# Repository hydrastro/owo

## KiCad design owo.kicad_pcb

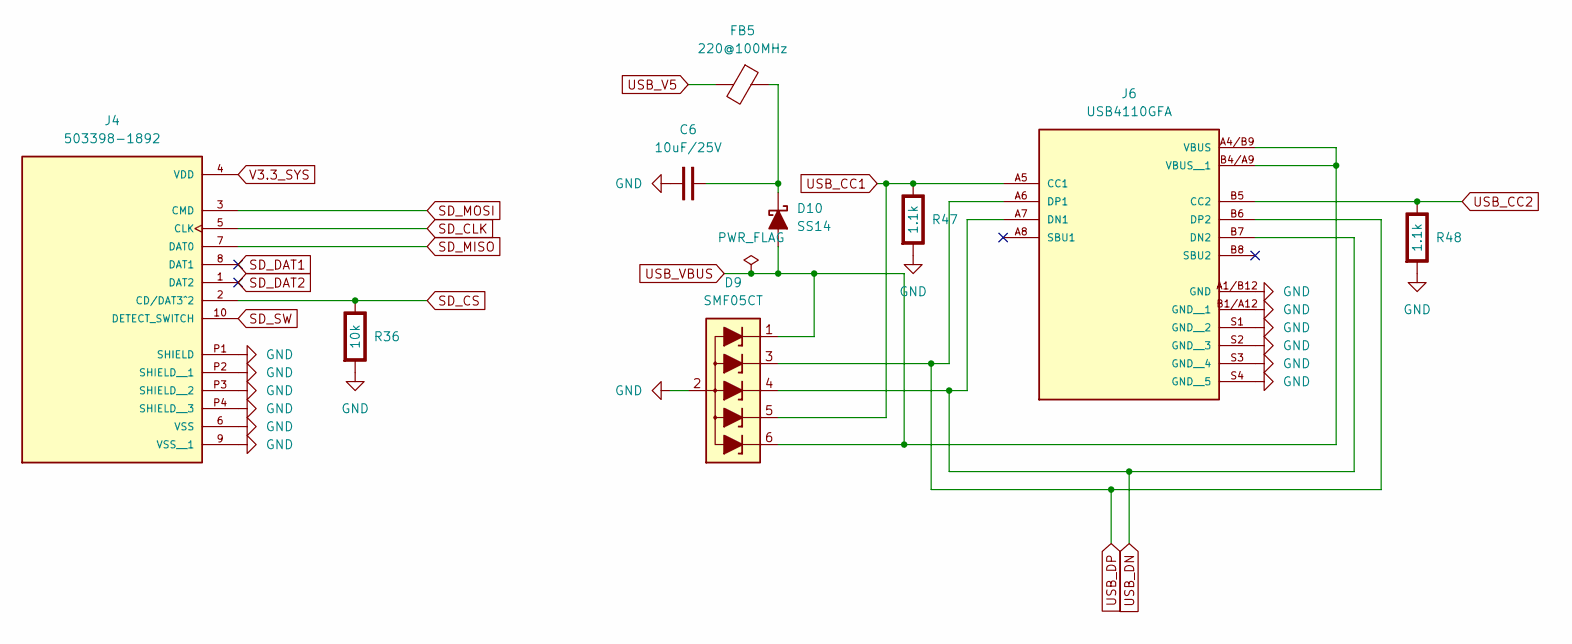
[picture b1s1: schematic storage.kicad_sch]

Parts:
C6: 10uF/25V; C_0805_2012Metric
D9: SMF05CT; SOT-363_SC-70-6
D10: SS14; D_SMA
FB5: 220@100MHz; Ferrite_0603_1608Metric
J4: 503398-1892; MOLEX_503398-1892; PARTREV 0
J6: USB4110GFA; GCT_USB4110GFA
R36: 10k; R_0603_1608Metric; Rating W
R47, R48: 1.1k; R_0603_1608Metric; Rating W

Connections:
unnamed: C6.2, D10.1 (K), FB5.1
SD_CLK: J4.5 (CLK); also elsewhere on the board
SD_CS: J4.2 (CD/DAT3^2), R36.1 (+); also elsewhere on the board
SD_DAT1: J4.8 (DAT1)
SD_DAT2: J4.1 (DAT2)
SD_MISO: J4.7 (DAT0); also elsewhere on the board
SD_MOSI: J4.3 (CMD); also elsewhere on the board
SD_SW: J4.10 (DETECT_SWITCH); also elsewhere on the board
USB_CC1: D9.5 (L4), J6.A5 (CC1), R47.1 (+)
USB_CC2: J6.B5 (CC2), R48.1 (+)
USB_DN: D9.4 (L3), J6.A7 (DN1), J6.B7 (DN2); also elsewhere on the board
USB_DP: D9.3 (L2), J6.A6 (DP1), J6.B6 (DP2); also elsewhere on the board
USB_V5: FB5.2; also elsewhere on the board
USB_VBUS: D9.1 (L1), D9.6 (L5), D10.2 (A), J6.A4/B9 (VBUS), J6.B4/A9 (VBUS__1)
V3.3_SYS: J4.4 (VDD); also elsewhere on the board

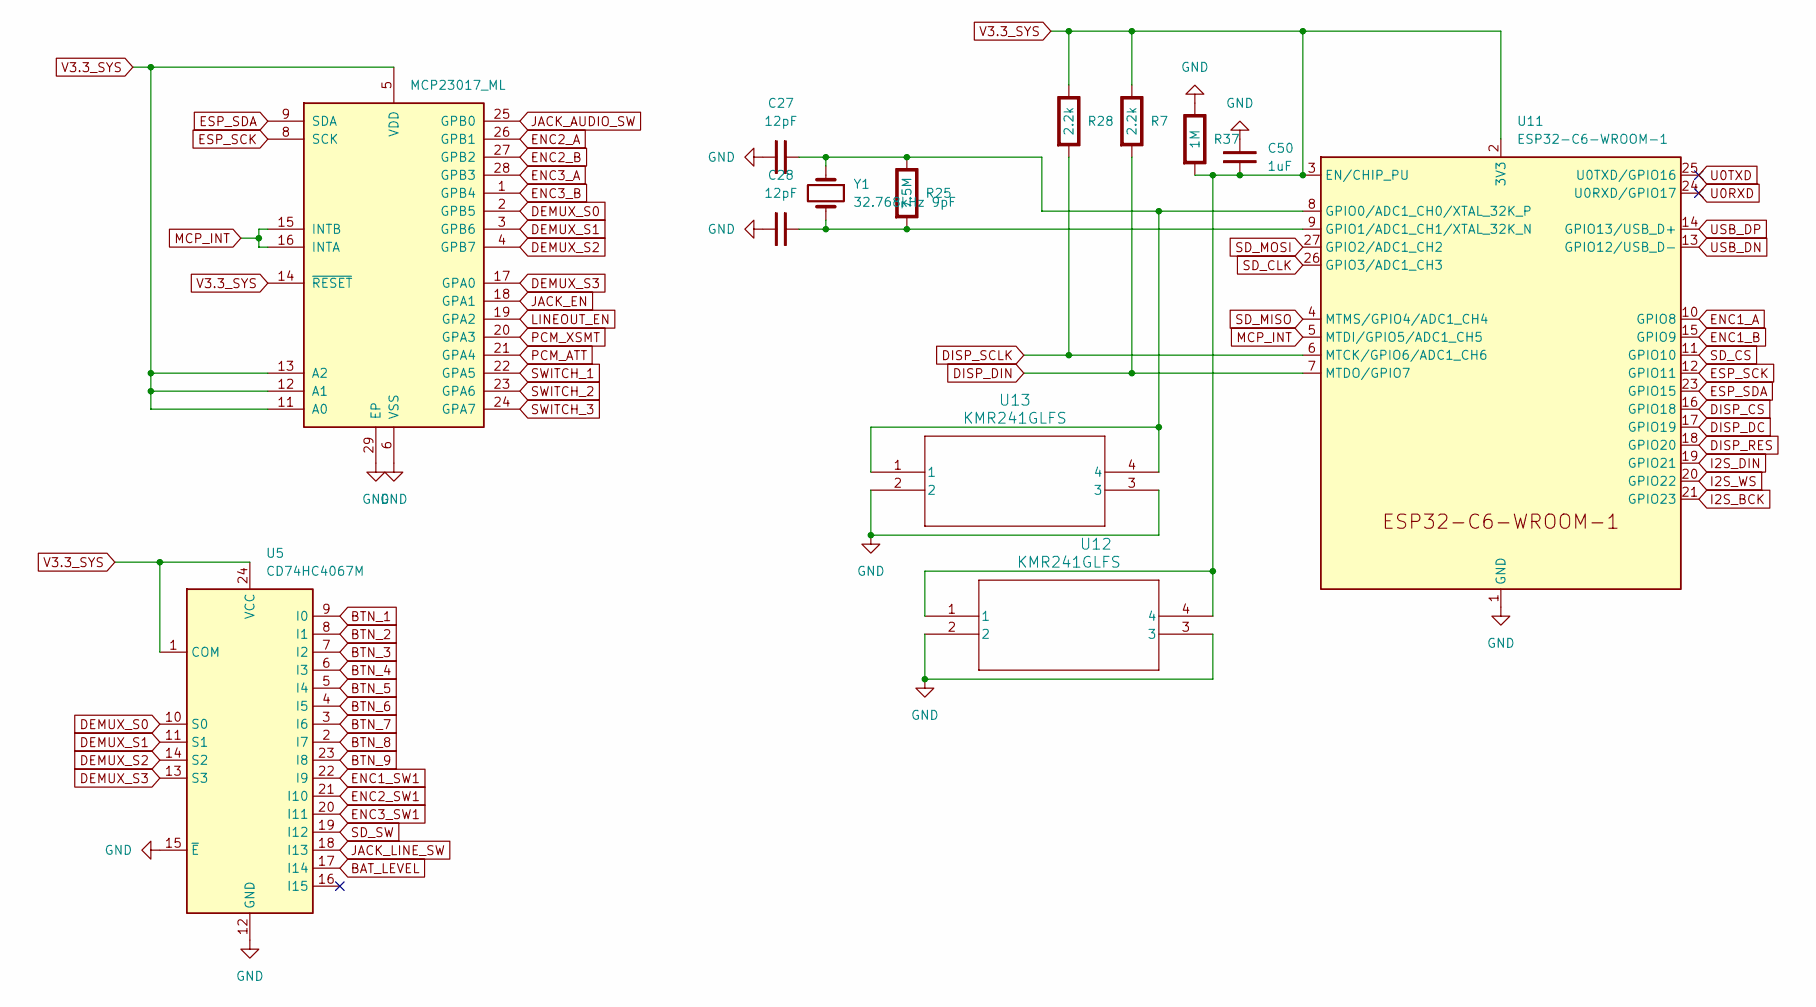
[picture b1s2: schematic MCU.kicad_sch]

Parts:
C27, C28: 12pF; C_0402_1005Metric
C50: 1uF; C_0603_1608Metric
R7, R28: 2.2k; R_0603_1608Metric; Rating W
R25: 7.5M; R_0603_1608Metric; Rating W
R37: 1M; R_0603_1608Metric; Rating W
U5: CD74HC4067M; SOIC-24W_7.5x15.4mm_P1.27mm
U10: MCP23017_ML; QFN-28-1EP_6x6mm_P0.65mm_EP4.25x4.25mm
U11: ESP32-C6-WROOM-1
U12, U13: KMR241GLFS; SWITCH_241GLFS
Y1: 32.768kHz 9pF; Crystal_SMD_0603-2Pin_6.0x3.5mm

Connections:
BAT_LEVEL: U5.17 (I14); also elsewhere on the board
BTN_1: U5.9 (I0); also elsewhere on the board
BTN_2: U5.8 (I1); also elsewhere on the board
BTN_3: U5.7 (I2); also elsewhere on the board
BTN_4: U5.6 (I3); also elsewhere on the board
BTN_5: U5.5 (I4); also elsewhere on the board
BTN_6: U5.4 (I5); also elsewhere on the board
BTN_7: U5.3 (I6); also elsewhere on the board
BTN_8: U5.2 (I7); also elsewhere on the board
BTN_9: U5.23 (I8); also elsewhere on the board
DEMUX_S0: U5.10 (S0), U10.2 (GPB5)
DEMUX_S1: U5.11 (S1), U10.3 (GPB6)
DEMUX_S2: U5.14 (S2), U10.4 (GPB7)
DEMUX_S3: U5.13 (S3), U10.17 (GPA0)
DISP_CS: U11.16 (GPIO18); also elsewhere on the board
DISP_DC: U11.17 (GPIO19); also elsewhere on the board
DISP_DIN: R7.2 (-), U11.7 (MTDO/GPIO7); also elsewhere on the board
DISP_RES: U11.18 (GPIO20); also elsewhere on the board
DISP_SCLK: R28.2 (-), U11.6 (MTCK/GPIO6/ADC1_CH6); also elsewhere on the board
ENC1_A: U11.10 (GPIO8); also elsewhere on the board
ENC1_B: U11.15 (GPIO9); also elsewhere on the board
ENC1_SW1: U5.22 (I9); also elsewhere on the board
ENC2_A: U10.26 (GPB1); also elsewhere on the board
ENC2_B: U10.27 (GPB2); also elsewhere on the board
ENC2_SW1: U5.21 (I10); also elsewhere on the board
ENC3_A: U10.28 (GPB3); also elsewhere on the board
ENC3_B: U10.1 (GPB4); also elsewhere on the board
ENC3_SW1: U5.20 (I11); also elsewhere on the board
ESP_SCK: U10.8 (SCK), U11.12 (GPIO11); also elsewhere on the board
ESP_SDA: U10.9 (SDA), U11.23 (GPIO15); also elsewhere on the board
I2S_BCK: U11.21 (GPIO23); also elsewhere on the board
I2S_DIN: U11.19 (GPIO21); also elsewhere on the board
I2S_WS: U11.20 (GPIO22); also elsewhere on the board
JACK_AUDIO_SW: U10.25 (GPB0); also elsewhere on the board
JACK_EN: U10.18 (GPA1); also elsewhere on the board
JACK_LINE_SW: U5.18 (I13); also elsewhere on the board
LINEOUT_EN: U10.19 (GPA2); also elsewhere on the board
MCP_INT: U10.15 (INTB), U10.16 (INTA), U11.5 (MTDI/GPIO5/ADC1_CH5)
unnamed: C27.2, R25.1 (+), U11.8 (GPIO0/ADC1_CH0/XTAL_32K_P), U13.1, U13.4, Y1.1
unnamed: C28.2, R25.2 (-), U11.9 (GPIO1/ADC1_CH1/XTAL_32K_N), Y1.2
PCM_ATT: U10.21 (GPA4); also elsewhere on the board
PCM_XSMT: U10.20 (GPA3); also elsewhere on the board
SD_CLK: U11.26 (GPIO3/ADC1_CH3); also elsewhere on the board
SD_CS: U11.11 (GPIO10); also elsewhere on the board
SD_MISO: U11.4 (MTMS/GPIO4/ADC1_CH4); also elsewhere on the board
SD_MOSI: U11.27 (GPIO2/ADC1_CH2); also elsewhere on the board
SD_SW: U5.19 (I12); also elsewhere on the board
SWITCH_1: U10.22 (GPA5); also elsewhere on the board
SWITCH_2: U10.23 (GPA6); also elsewhere on the board
SWITCH_3: U10.24 (GPA7); also elsewhere on the board
U0RXD: U11.24 (U0RXD/GPIO17)
U0TXD: U11.25 (U0TXD/GPIO16)
USB_DN: U11.13 (GPIO12/USB_D-); also elsewhere on the board
USB_DP: U11.14 (GPIO13/USB_D+); also elsewhere on the board
V3.3_SYS: C50.1, R7.1 (+), R28.1 (+), R37.2 (-), U5.1 (COM), U5.24 (VCC), U10.5 (VDD), U10.11 (A0), U10.12 (A1), U10.13 (A2), U10.14 (~RESET), U11.2 (3V3), U11.3 (EN/CHIP_PU), U12.1, U12.4; also elsewhere on the board

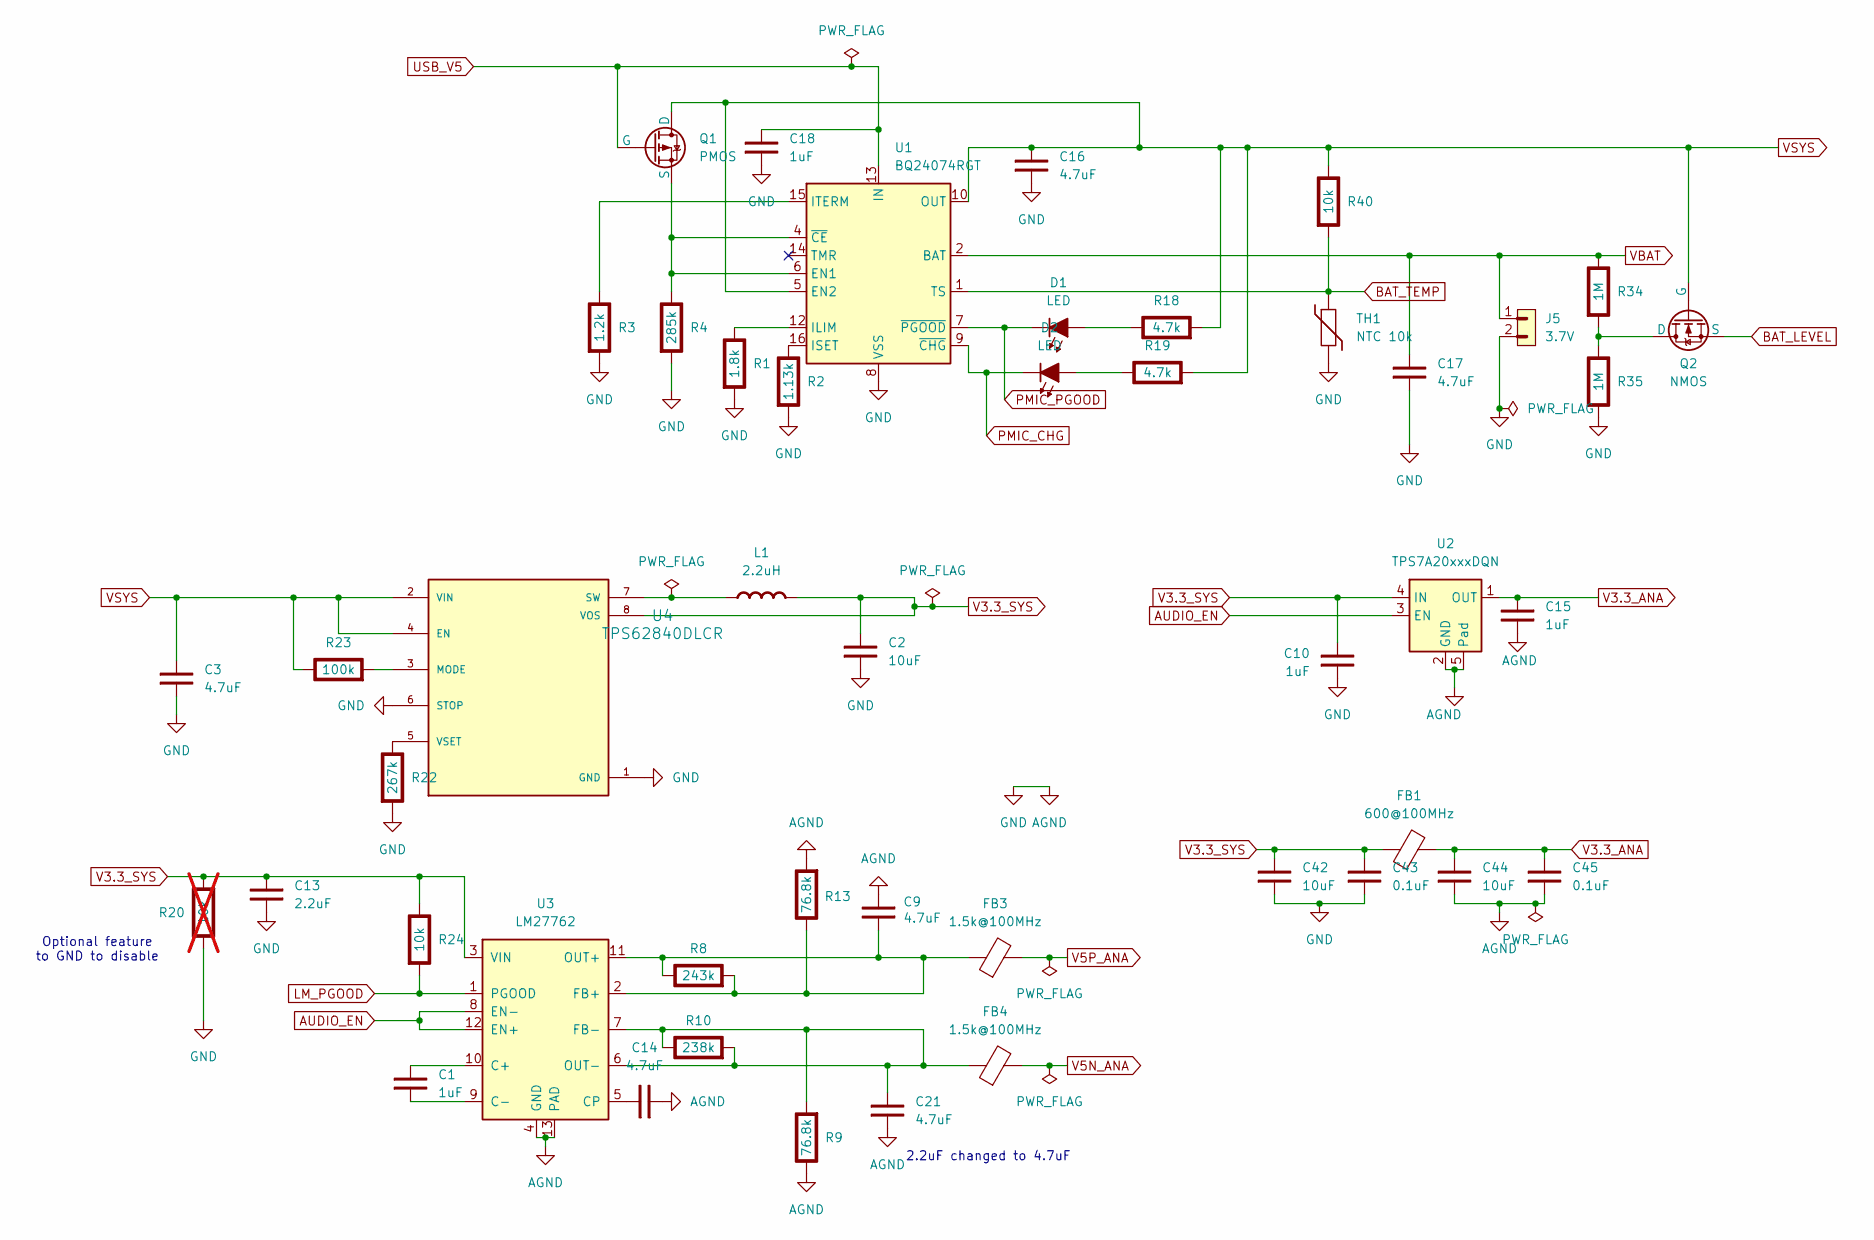
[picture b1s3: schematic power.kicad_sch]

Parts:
C1, C10, C15, C18: 1uF; C_0603_1608Metric
C2: 10uF; C_0805_2012Metric
C3, C9, C14, C16, C17, C21: 4.7uF; C_0603_1608Metric
C13: 2.2uF; C_0603_1608Metric
C42, C44: 10uF; CP_EIA-3528-21_Kemet-B
C43, C45: 0.1uF; C_0603_1608Metric
D1, D2: LED; LED_PLCC-2_2216
FB1: 600@100MHz; Ferrite_0805_2012Metric
FB3, FB4: 1.5k@100MHz; Ferrite_0603_1608Metric
J5: 3.7V; CONN_B2B-ZR-SM4-TF_JST
L1: 2.2uH; L_1008_2520Metric; Rating A
Q1: PMOS; SOT-23
Q2: NMOS; SOT-23
R1: 1.8k; R_0603_1608Metric; Rating W
R2: 1.13k; R_0603_1608Metric; Rating W
R3: 1.2k; R_0603_1608Metric; Rating W
R4: 285k; R_0603_1608Metric; Rating W
R8: 243k; R_0603_1608Metric; Rating W
R9, R13: 76.8k; R_0603_1608Metric; Rating W
R10: 238k; R_0603_1608Metric; Rating W
R18, R19: 4.7k; R_0603_1608Metric; Rating W
R20: 10k; R_0603_1608Metric; Rating W; not fitted
R22: 267k; R_0603_1608Metric; Rating W
R23: 100k; R_0603_1608Metric; Rating W
R24, R40: 10k; R_0603_1608Metric; Rating W
R34, R35: 1M; R_0603_1608Metric; Rating W
TH1: NTC 10k; R_0603_1608Metric
U1: BQ24074RGT; VQFN-16-1EP_3x3mm_P0.5mm_EP1.6x1.6mm
U2: TPS7A20xxxDQN; Texas_X2SON-4_1x1mm_P0.65mm
U3: LM27762; WSON-12-1EP_3x2mm_P0.5mm_EP1x2.65_ThermalVias
U4: TPS62840DLCR; SON50P200X150X100-8N

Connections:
AUDIO_EN: U2.3 (EN), U3.8 (EN-), U3.12 (EN+)
BAT_LEVEL: Q2.3 (S); also elsewhere on the board
BAT_TEMP: R40.2 (-), TH1.1, U1.1 (TS)
LM_PGOOD: R24.2 (-), U3.1 (PGOOD)
unnamed: D1.2 (A), R18.1 (+)
unnamed: D2.2 (A), R19.1 (+)
unnamed: L1.1 (+), U4.7 (SW)
unnamed: Q1.3 (S), R4.1 (+), U1.4 (~CE), U1.6 (EN1)
unnamed: Q2.1 (D), R34.2 (-), R35.1 (+)
unnamed: R1.1 (+), U1.12 (ILIM)
unnamed: R2.1 (+), U1.16 (ISET)
unnamed: R3.1 (+), U1.15 (ITERM)
unnamed: C21.2, FB4.1, R9.2 (-), R10.1 (+), R10.2 (-), U3.6 (OUT-), U3.7 (FB-)
unnamed: C9.2, FB3.1, R8.1 (+), R8.2 (-), R13.1 (+), U3.2 (FB+), U3.11 (OUT+)
unnamed: R22.1 (+), U4.5 (VSET)
unnamed: R23.2 (-), U4.3 (MODE)
unnamed: C1.2, U3.10 (C+)
unnamed: C1.1, U3.9 (C-)
unnamed: C14.2, U3.5 (CP)
PMIC_CHG: D2.1 (K), U1.9 (~CHG)
PMIC_PGOOD: D1.1 (K), U1.7 (~PGOOD)
USB_V5: C18.2, Q1.2 (G), U1.13 (IN); also elsewhere on the board
V3.3_ANA: C15.1, C44.2, C45.2, FB1.2, U2.1 (OUT); also elsewhere on the board
V3.3_SYS: C2.2, C10.2, C13.1, C42.2, C43.2, FB1.1, L1.2 (-), R20.2 (-), R24.1 (+), U2.4 (IN), U3.3 (VIN), U4.8 (VOS); also elsewhere on the board
V5N_ANA: FB4.2; also elsewhere on the board
V5P_ANA: FB3.2; also elsewhere on the board
VBAT: C17.2, J5.1, R34.1 (+), U1.2 (BAT), U1.3 (BAT)
VSYS: C3.2, C16.2, Q1.1 (D), Q2.2 (G), R18.2 (-), R19.2 (-), R23.1 (+), R40.1 (+), U1.5 (EN2), U1.10 (OUT), U1.11 (OUT), U4.2 (VIN), U4.4 (EN)

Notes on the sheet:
Optional feature to GND to disable
2.2uF changed to 4.7uF

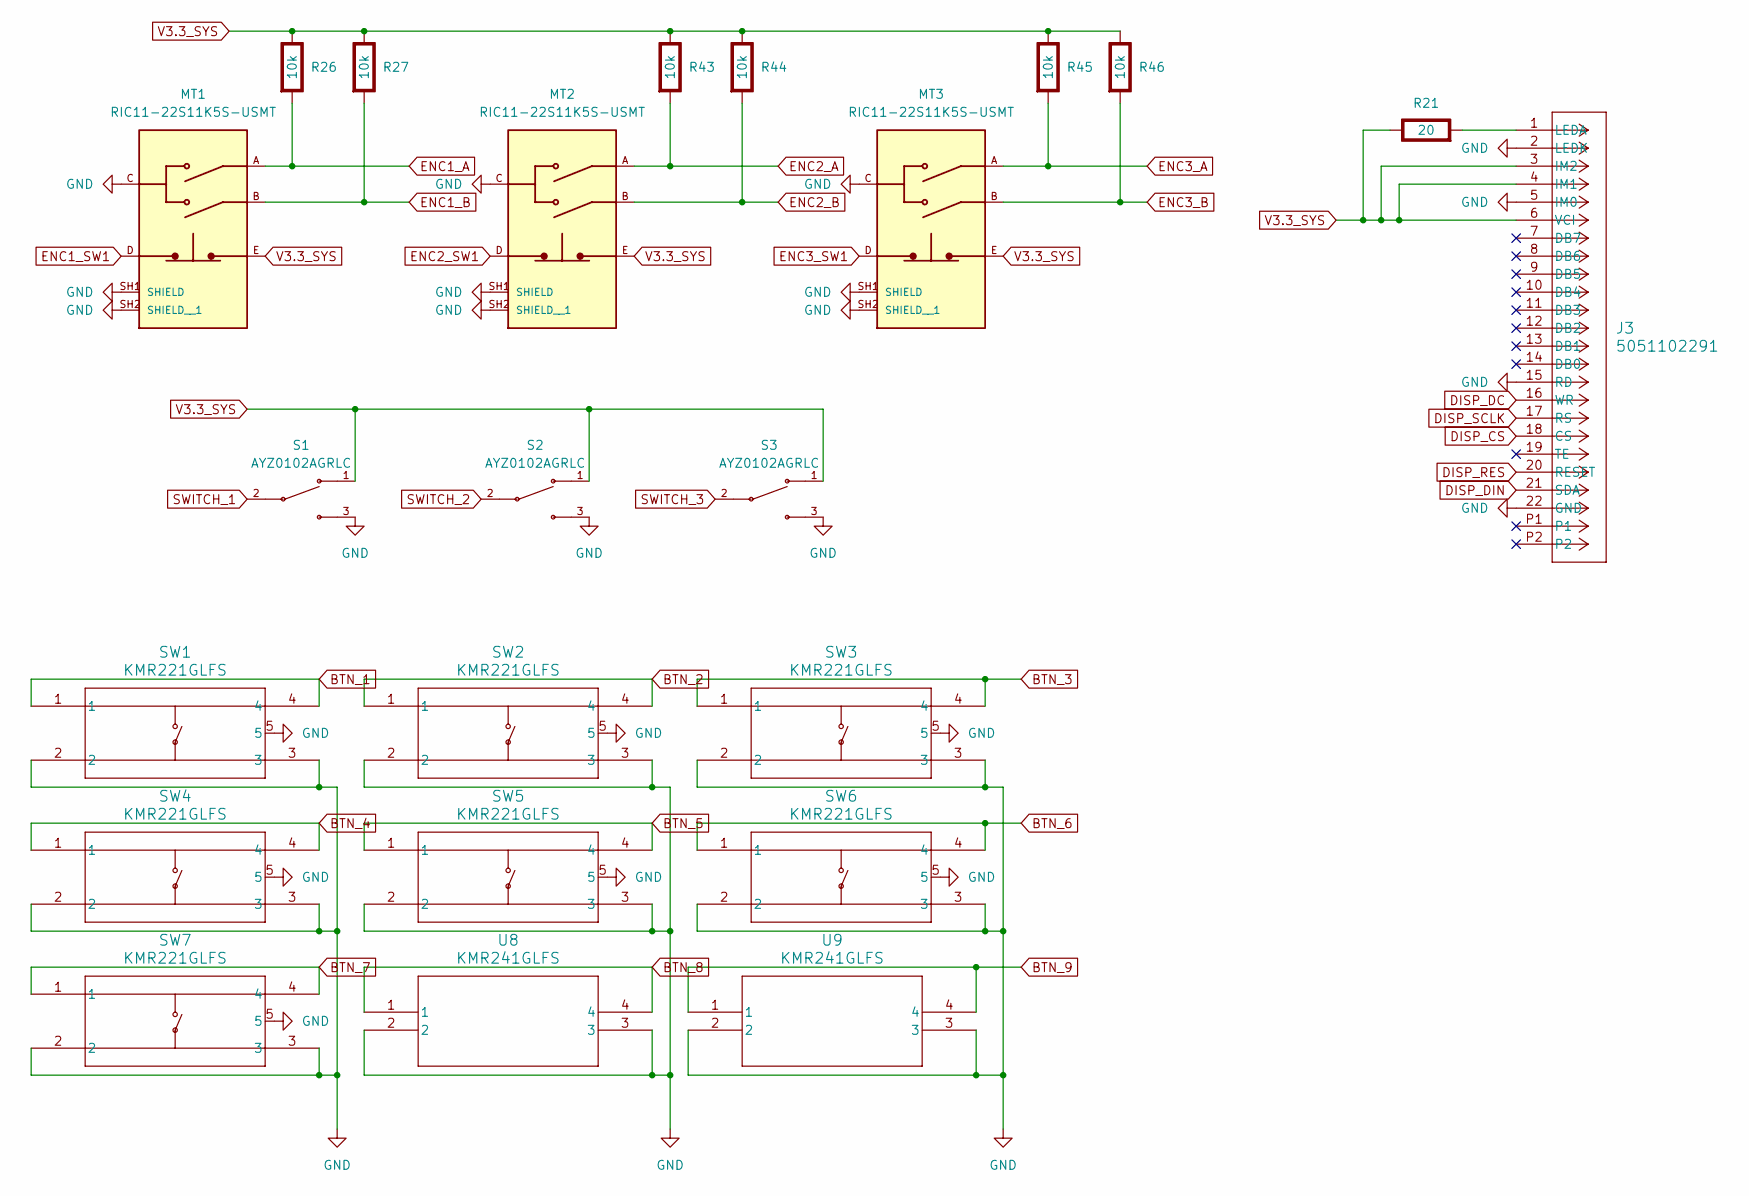
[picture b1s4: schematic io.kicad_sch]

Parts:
J3: 5051102291; CON_5051102291_MOL
MT1, MT2, MT3: RIC11-22S11K5S-USMT; XDCR_RIC11-22S11K5S-USMT; PARTREV 1.01
R21: 20; R_0603_1608Metric; Rating W
R26, R27, R43, R44, R45, R46: 10k; R_0603_1608Metric; Rating W
S1, S2, S3: AYZ0102AGRLC; SW_AYZ0102AGRLC
SW1, SW2, SW3, SW4, SW5, SW6, SW7: KMR221GLFS; SW4_KMR221GLFS_CNK
U8, U9: KMR241GLFS; SWITCH_241GLFS

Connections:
BTN_1: SW1.1, SW1.4; also elsewhere on the board
BTN_2: SW2.1, SW2.4; also elsewhere on the board
BTN_3: SW3.1, SW3.4; also elsewhere on the board
BTN_4: SW4.1, SW4.4; also elsewhere on the board
BTN_5: SW5.1, SW5.4; also elsewhere on the board
BTN_6: SW6.1, SW6.4; also elsewhere on the board
BTN_7: SW7.1, SW7.4; also elsewhere on the board
BTN_8: U8.1, U8.4; also elsewhere on the board
BTN_9: U9.1, U9.4; also elsewhere on the board
DISP_CS: J3.18 (CS); also elsewhere on the board
DISP_DC: J3.16 (WR); also elsewhere on the board
DISP_DIN: J3.21 (SDA); also elsewhere on the board
DISP_RES: J3.20 (RESET); also elsewhere on the board
DISP_SCLK: J3.17 (RS); also elsewhere on the board
ENC1_A: MT1.A, R26.2 (-); also elsewhere on the board
ENC1_B: MT1.B, R27.2 (-); also elsewhere on the board
ENC1_SW1: MT1.D; also elsewhere on the board
ENC2_A: MT2.A, R43.2 (-); also elsewhere on the board
ENC2_B: MT2.B, R44.2 (-); also elsewhere on the board
ENC2_SW1: MT2.D; also elsewhere on the board
ENC3_A: MT3.A, R45.2 (-); also elsewhere on the board
ENC3_B: MT3.B, R46.2 (-); also elsewhere on the board
ENC3_SW1: MT3.D; also elsewhere on the board
unnamed: J3.1 (LEDA), R21.2 (-)
SWITCH_1: S1.2; also elsewhere on the board
SWITCH_2: S2.2; also elsewhere on the board
SWITCH_3: S3.2; also elsewhere on the board
V3.3_SYS: J3.3 (IM2), J3.4 (IM1), J3.6 (VCI), MT1.E, MT2.E, MT3.E, R21.1 (+), R26.1 (+), R27.1 (+), R43.1 (+), R44.1 (+), R45.1 (+), R46.1 (+), S1.1, S2.1, S3.1; also elsewhere on the board

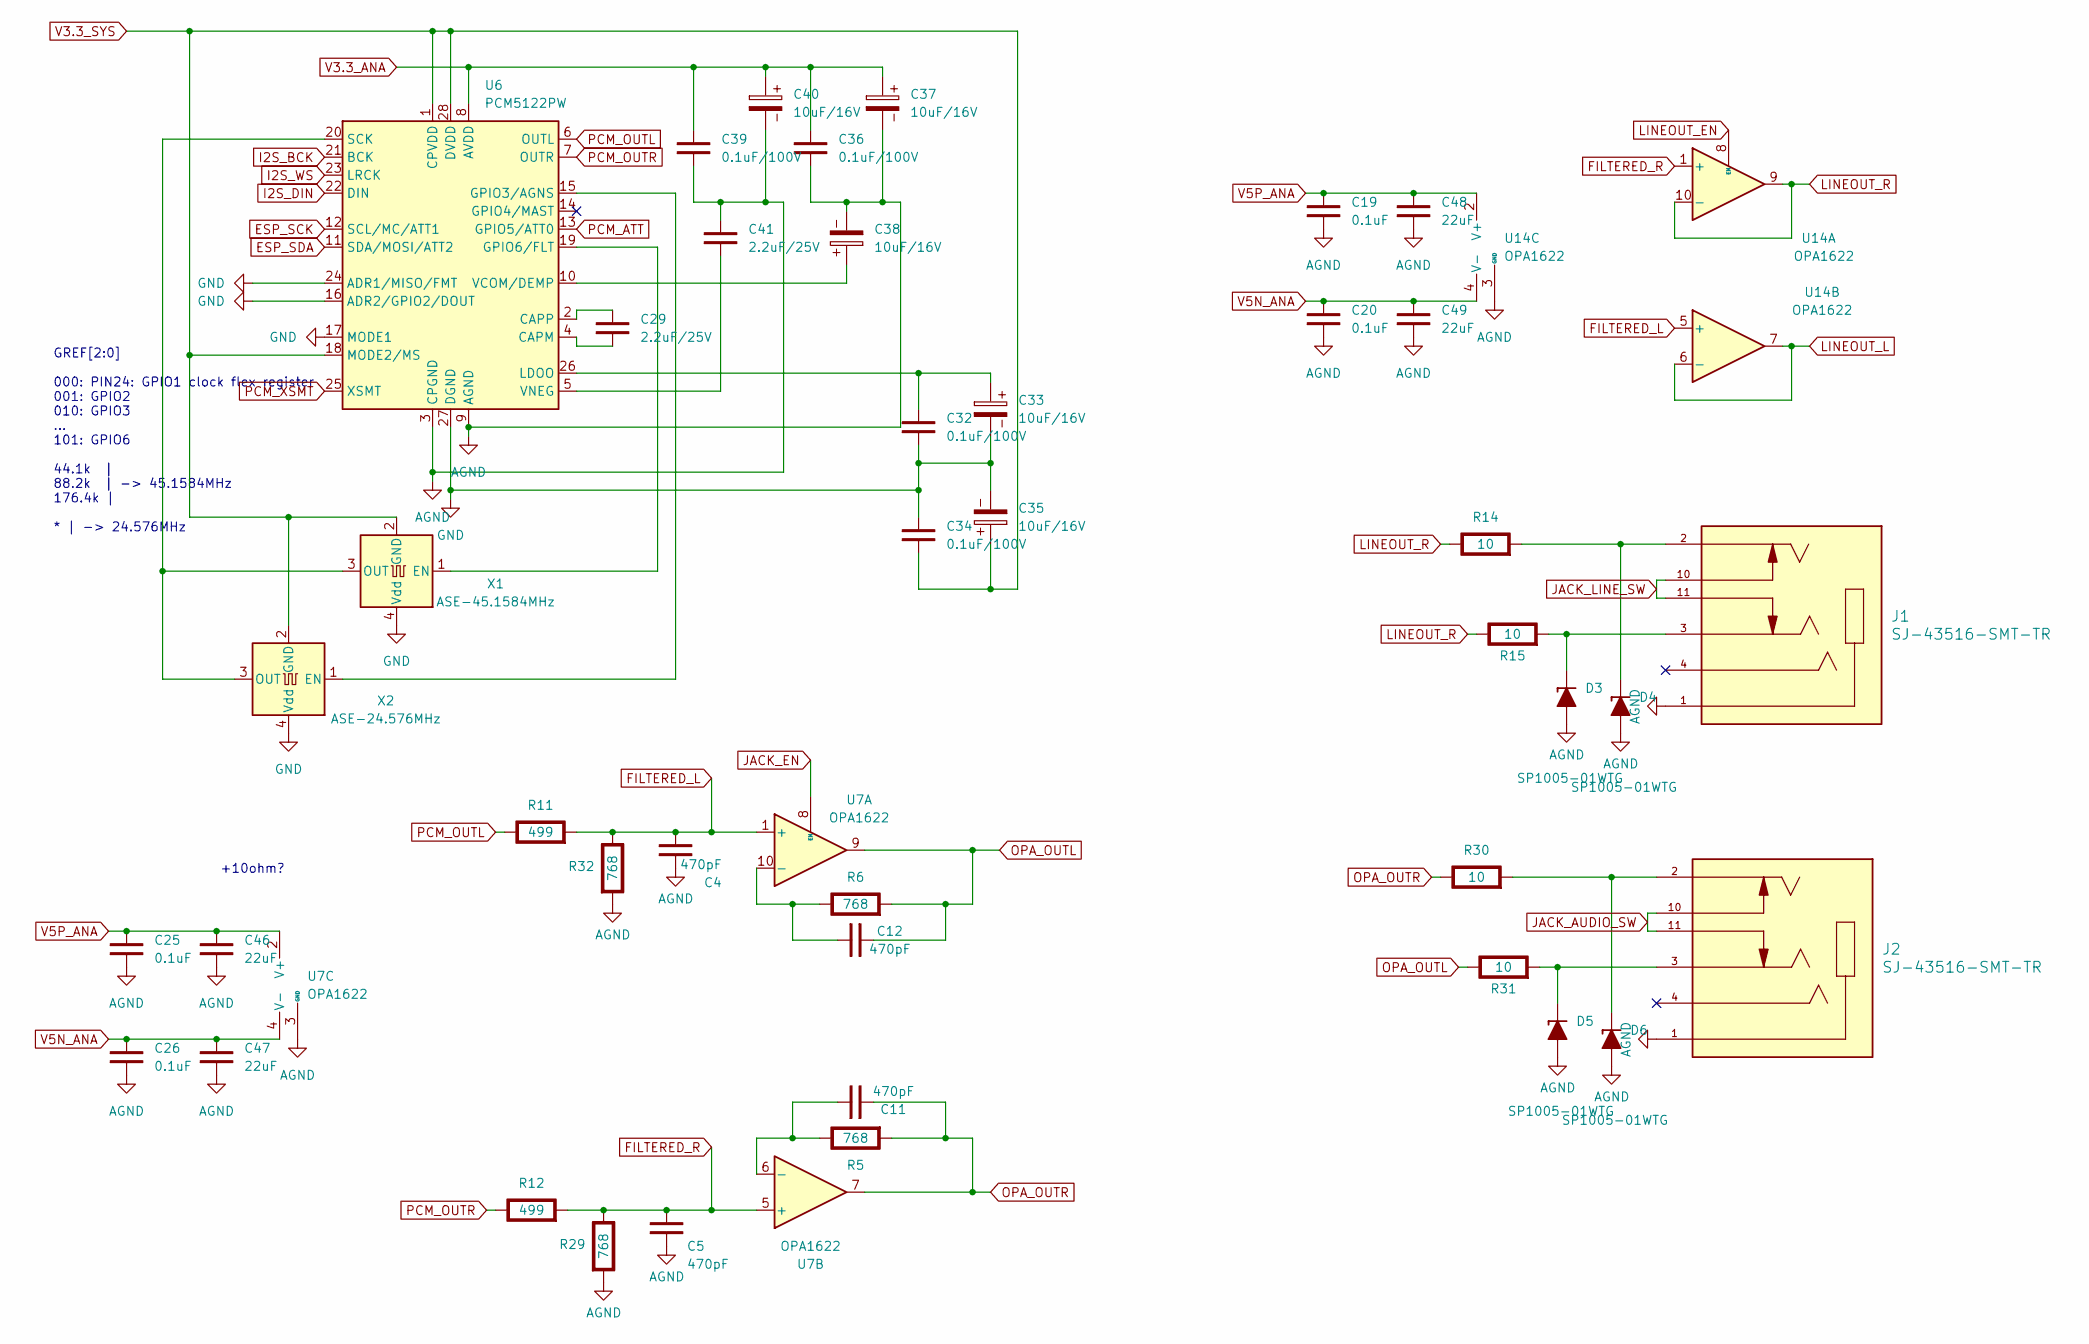
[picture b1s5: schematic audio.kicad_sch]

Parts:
C4, C5, C11, C12: 470pF; C_0402_1005Metric
C19, C20, C25, C26: 0.1uF; C_0805_2012Metric
C29, C41: 2.2uF/25V; C_0603_1608Metric
C32, C34, C36, C39: 0.1uF/100V; C_0805_2012Metric
C33, C35, C37, C38, C40: 10uF/16V; CP_EIA-3528-21_Kemet-B
C46, C47, C48, C49: 22uF; C_0805_2012Metric
D3, D4, D5, D6: SP1005-01WTG; D_0201_0603Metric
J1, J2: SJ-43516-SMT-TR; CUI_SJ2-35894D-SMT-TR; PARTREV 1.04
R5, R6, R29, R32: 768; R_0603_1608Metric; Rating W
R11, R12: 499; R_0603_1608Metric; Rating W
R14, R15, R30, R31: 10; R_0603_1608Metric; Rating W
U6: PCM5122PW; TSSOP-28_4.4x9.7mm_P0.65mm
U7, U14: OPA1622; Texas_S-PVSON-N10
X1: ASE-45.1584MHz; Oscillator_SMD_Abracon_ASE-4Pin_3.2x2.5mm
X2: ASE-24.576MHz; Oscillator_SMD_Abracon_ASE-4Pin_3.2x2.5mm

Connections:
ESP_SCK: U6.12 (SCL/MC/ATT1); also elsewhere on the board
ESP_SDA: U6.11 (SDA/MOSI/ATT2); also elsewhere on the board
FILTERED_L: C4.2, R11.2 (-), R32.1 (+), U7.1 (+), U14.5 (+)
FILTERED_R: C5.2, R12.2 (-), R29.1 (+), U7.5 (+), U14.1 (+)
I2S_BCK: U6.21 (BCK); also elsewhere on the board
I2S_DIN: U6.22 (DIN); also elsewhere on the board
I2S_WS: U6.23 (LRCK); also elsewhere on the board
JACK_AUDIO_SW: J2.10, J2.11; also elsewhere on the board
JACK_EN: U7.8 (EN); also elsewhere on the board
JACK_LINE_SW: J1.10, J1.11; also elsewhere on the board
LINEOUT_EN: U14.8 (EN); also elsewhere on the board
LINEOUT_L: U14.6 (-), U14.7
LINEOUT_R: R14.1 (+), R15.1 (+), U14.9, U14.10 (-)
unnamed: D3.1 (K), J1.3, R15.2 (-)
unnamed: D4.1 (K), J1.2, R14.2 (-)
unnamed: D5.1 (K), J2.3, R31.2 (-)
unnamed: D6.1 (K), J2.2, R30.2 (-)
unnamed: C11.1, R5.1 (+), U7.6 (-)
unnamed: C12.1, R6.1 (+), U7.10 (-)
unnamed: C29.1, U6.4 (CAPM)
unnamed: C29.2, U6.2 (CAPP)
unnamed: U6.15 (GPIO3/AGNS), X2.1 (EN)
unnamed: U6.19 (GPIO6/FLT), X1.1 (EN)
unnamed: C32.2, C33.1, U6.26 (LDOO)
unnamed: U6.20 (SCK), X1.3 (OUT), X2.3 (OUT)
unnamed: C38.1, U6.10 (VCOM/DEMP)
unnamed: C41.1, U6.5 (VNEG)
OPA_OUTL: C12.2, R6.2 (-), R31.1 (+), U7.9
OPA_OUTR: C11.2, R5.2 (-), R30.1 (+), U7.7
PCM_ATT: U6.13 (GPIO5/ATT0); also elsewhere on the board
PCM_OUTL: R11.1 (+), U6.6 (OUTL)
PCM_OUTR: R12.1 (+), U6.7 (OUTR)
PCM_XSMT: U6.25 (XSMT); also elsewhere on the board
V3.3_ANA: C36.2, C37.1, C39.2, C40.1, U6.8 (AVDD); also elsewhere on the board
V3.3_SYS: C34.1, C35.1, U6.1 (CPVDD), U6.18 (MODE2/MS), U6.28 (DVDD), X1.2 (GND), X2.2 (GND); also elsewhere on the board
V5N_ANA: C20.2, C26.2, C47.2, C49.2, U7.4 (V-), U7.11 (V-), U14.4 (V-), U14.11 (V-); also elsewhere on the board
V5P_ANA: C19.2, C25.2, C46.2, C48.2, U7.2 (V+), U14.2 (V+); also elsewhere on the board

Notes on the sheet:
+10ohm?
GREF[2:0] 000: PIN24: GPIO1 clock flex register 001: GPIO2 010: GPIO3 ... 101: GPIO6 44.1k | 88.2k | -> 45.1584MHz 176.4k | * | -> 24.576MHz

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
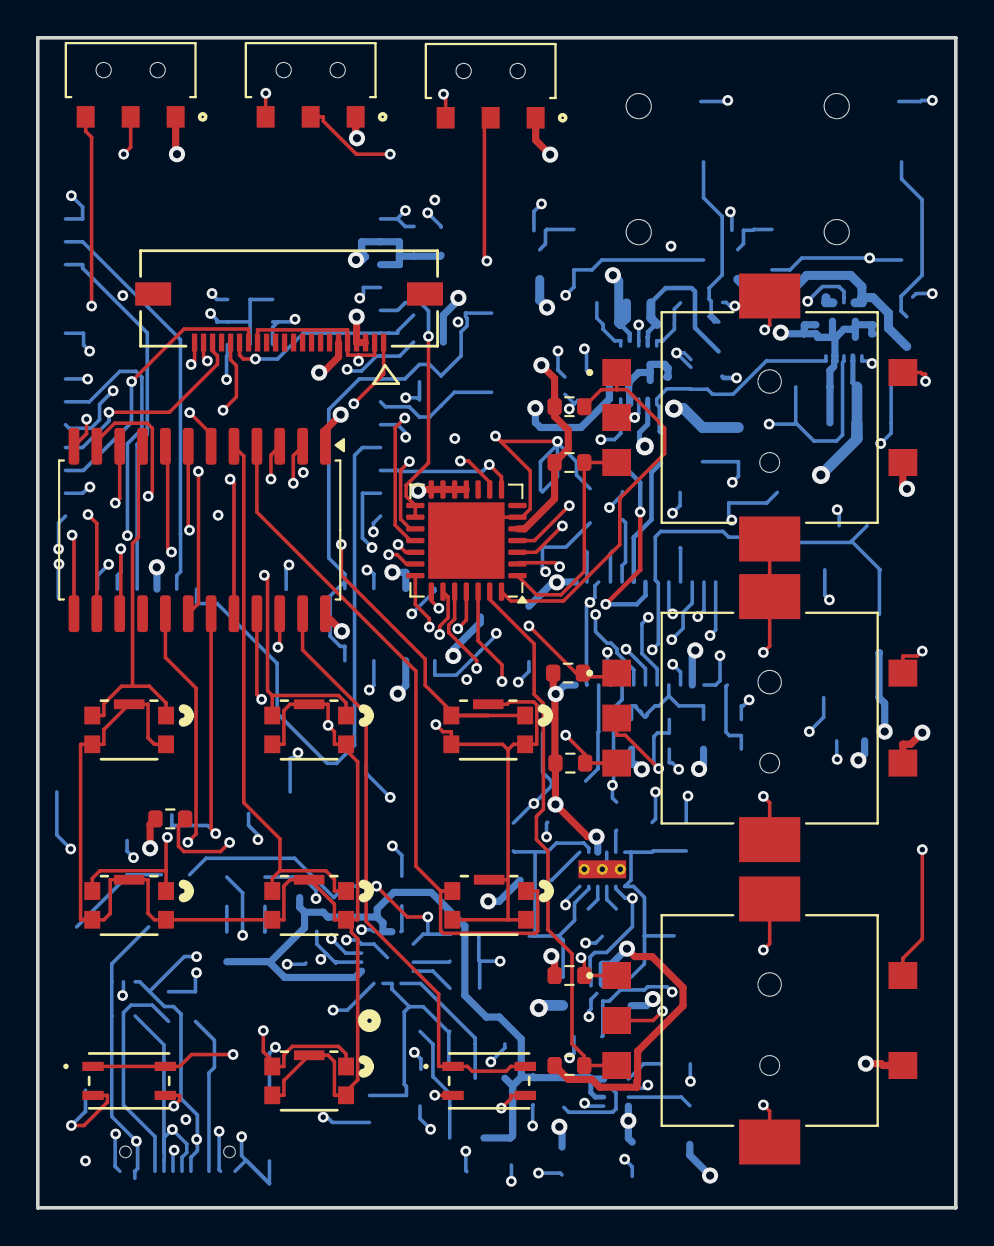
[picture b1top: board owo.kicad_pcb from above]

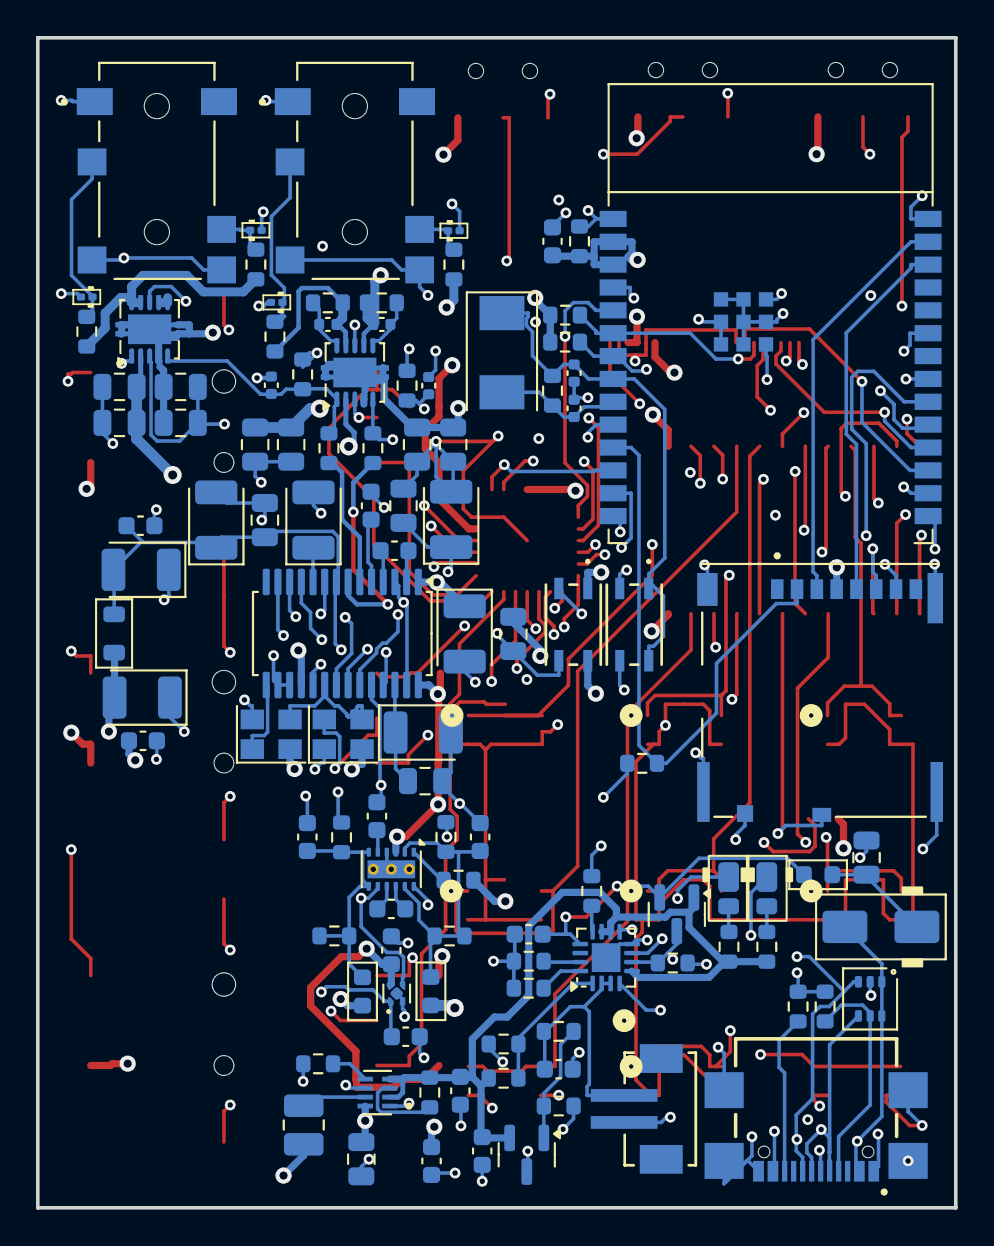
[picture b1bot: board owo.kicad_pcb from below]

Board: 6 copper layers, 51.0 x 65.0 mm, 135 parts (110 on the bottom side), 108 nets.

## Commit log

2025-06-05 uwu owo twt
2025-06-05 project file
2025-06-07 pcb / inital work
2025-06-07 ICs placed
2025-06-10 all pcb elements positioned + minor schematics changes
2025-06-10 tracing ground and some power planes
2025-06-11 changing ic placement
2025-06-16 routing
2025-06-16 more routing
2025-08-03 non ci sono parole adatte a descrivere la mia sofferenza
